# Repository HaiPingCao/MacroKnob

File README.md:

# ControlDeck

ControlDeck is a simple, multi-purpose, programmable volume knob built with an Arduino Pro Micro.  
It is designed as a compact hardware control interface for volume adjustment, mode switching, and custom hotkeys.

! Please ignore the grammar error, my English is bad 😭

## Hardware

The project uses the following components:

- Arduino Pro Micro
- Rotary encoder with integrated push button
- 4 momentary push buttons
- SSD1306 OLED display (128×64)

### Circuit Setup and Wiring

| Component   | Pin | Description                                  |
| ----------- | --- | -------------------------------------------- |
| Encoder CLK | 5   | Clock signal for rotation detection          |
| Encoder DT  | 4   | Data signal for rotation direction detection |
| Encoder SW  | 6   | Encoder push button                          |
| UP Button   | 10  | Switch to previous mode                      |
| DOWN Button | 16  | Switch to next mode                          |
| # Button    | 14  | Special function button                      |
| \* Button   | 15  | Triggers Win + Ctrl + Alt + F5 hotkey        |

## Software

### Required Libraries

When using the Arduino IDE, install the following libraries via the Arduino Library Manager:

- **HID-Project** by NicoHood
- **Adafruit GFX Library** by Adafruit
- **Adafruit SSD1306** by Adafruit

### Driver Development

A new custom driver written in Rust is currently in early development to support more advanced features.  
See the `mk-driver` directory for details.

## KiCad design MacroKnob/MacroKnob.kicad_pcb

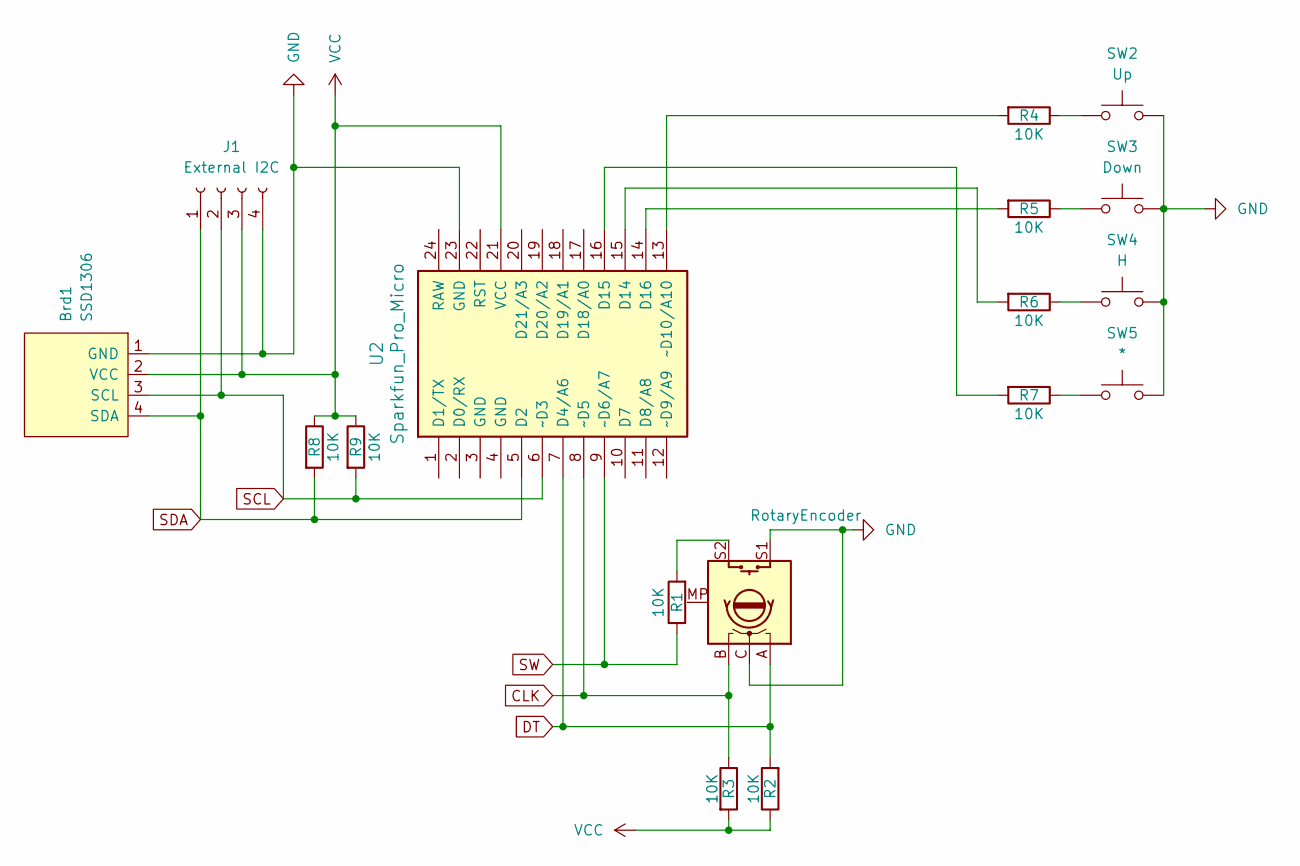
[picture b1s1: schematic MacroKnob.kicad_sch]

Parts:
Brd1: SSD1306; 128x64OLED
J1: External I2C; Hirose_DF13-04P-1.25DSA_1x04_P1.25mm_Vertical
R1, R2, R3, R4, R5, R6, R7, R8, R9: 10K; R_Axial_DIN0204_L3.6mm_D1.6mm_P5.08mm_Horizontal
SW1: RotaryEncoder; RotaryEncoder_Alps_EC11E-Switch_Vertical_H20mm
SW2: Up; SW_SPST_CK_RS282G05A3
SW3: Down; SW_SPST_CK_RS282G05A3
SW4: H; SW_SPST_CK_RS282G05A3
SW5: *; SW_SPST_CK_RS282G05A3
U2: Sparkfun_Pro_Micro

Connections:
CLK: R3.1, SW1.B, U2.8 (~D5)
DT: R2.2, SW1.A, U2.7 (D4/A6)
GND: Brd1.1 (GND), J1.4, SW1.C, SW1.S1, SW2.2, SW3.2, SW4.2, SW5.2, U2.23 (GND)
unnamed: R1.2, SW1.S2
unnamed: R4.1, SW2.1
unnamed: R5.1, SW3.1
unnamed: R6.1, SW4.1
unnamed: R7.1, SW5.1
unnamed: R6.2, U2.15 (D14)
unnamed: R7.2, U2.16 (D15)
unnamed: R5.2, U2.14 (D16)
unnamed: R4.2, U2.13 (~D10/A10)
SCL: Brd1.3 (SCL), J1.2, R9.2, U2.6 (~D3)
SDA: Brd1.4 (SDA), J1.1, R8.2, U2.5 (D2)
SW: R1.1, U2.9 (~D6/A7)
VCC: Brd1.2 (VCC), J1.3, R2.1, R3.2, R8.1, R9.1, U2.21 (VCC)

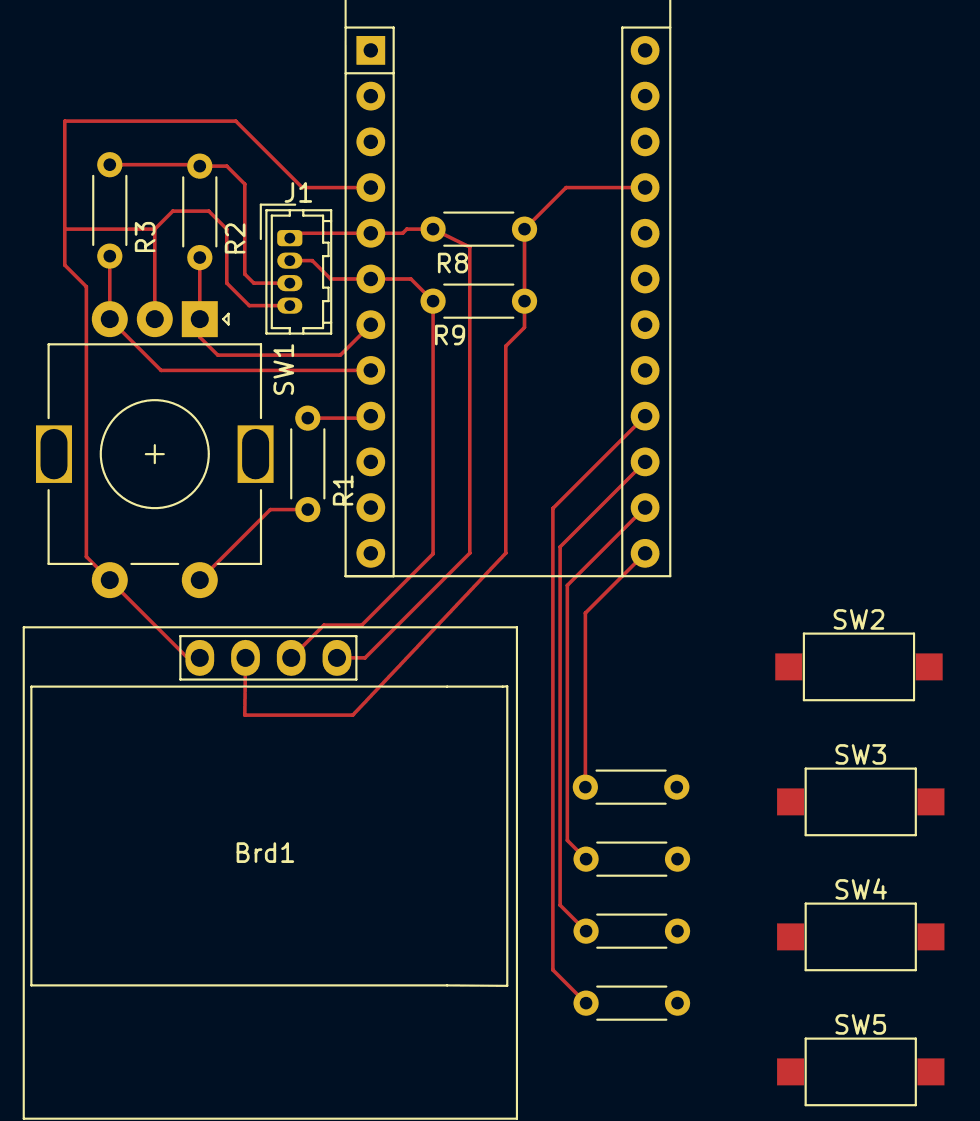
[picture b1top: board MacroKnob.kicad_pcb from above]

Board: 2 copper layers, 17 parts (0 on the bottom side), 16 nets.

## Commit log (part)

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2025-06-23 update schematic & pcb
2025-06-23 Update Schematic
2025-06-23 Add Script for arduino
2025-10-03 modified: MacroKnob/MacroKnob.kicad_pro modified: README.md
2026-01-14 add windows platform
2026-01-14 add readme md for the driver repo
2026-01-14 modified: .gitignore new file: mk-driver/Cargo.toml new file: mk-driver/readme.md new file: mk-driver/src/arduino.rs new file: mk-driver/src/linux/mod.rs new file: mk-driver/src/linux/volume_action_l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
2026-01-14 update readme for mk-driver
